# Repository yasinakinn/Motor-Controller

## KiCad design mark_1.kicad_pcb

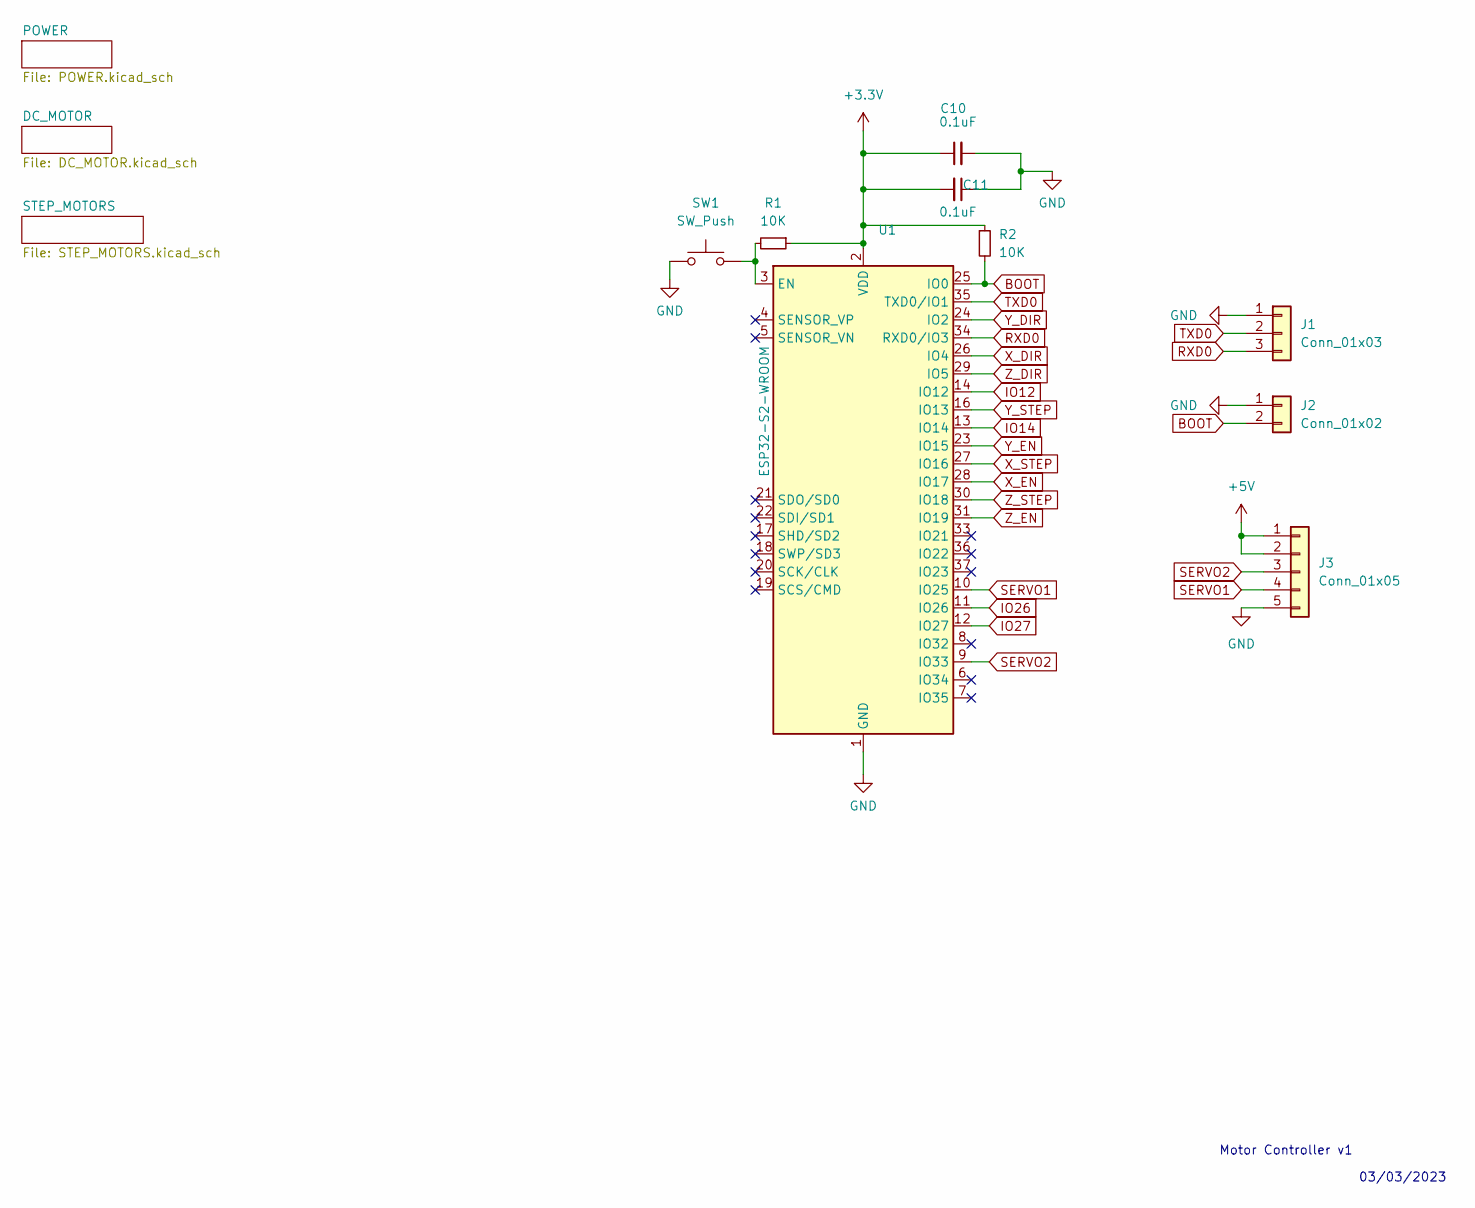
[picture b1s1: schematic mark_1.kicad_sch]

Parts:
C10, C11: 0.1uF; C_0805_2012Metric
J1: Conn_01x03; PinHeader_1x03_P2.54mm_Vertical
J2: Conn_01x02; PinHeader_1x02_P2.54mm_Vertical
J3: Conn_01x05; PhoenixContact_MC_1,5_5-G-3.81_1x05_P3.81mm_Horizontal
R1, R2: 10K; R_0805_2012Metric
SW1: SW_Push; SW_Push_1P1T_NO_6x6mm_H9.5mm
U1: ESP32-S2-WROOM; ESP32-WROOM-32

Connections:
+3.3V: C10.1, C11.2, R1.1, R2.1, U1.2 (VDD); also elsewhere on the board
+5V: J3.1, J3.2; also elsewhere on the board
BOOT: J2.2, R2.2, U1.25 (IO0)
GND: C10.2, C11.1, J1.1, J2.1, J3.5, SW1.1, U1.1 (GND), U1.15 (GND), U1.38 (GND), U1.39 (GND); also elsewhere on the board
IO12: U1.14 (IO12); also elsewhere on the board
IO14: U1.13 (IO14); also elsewhere on the board
IO26: U1.11 (IO26); also elsewhere on the board
IO27: U1.12 (IO27); also elsewhere on the board
unnamed: R1.2, SW1.2, U1.3 (EN)
RXD0: J1.3, U1.34 (RXD0/IO3)
SERVO1: J3.4, U1.10 (IO25)
SERVO2: J3.3, U1.9 (IO33)
TXD0: J1.2, U1.35 (TXD0/IO1)
X_DIR: U1.26 (IO4); also elsewhere on the board
X_EN: U1.28 (IO17); also elsewhere on the board
X_STEP: U1.27 (IO16); also elsewhere on the board
Y_DIR: U1.24 (IO2); also elsewhere on the board
Y_EN: U1.23 (IO15); also elsewhere on the board
Y_STEP: U1.16 (IO13); also elsewhere on the board
Z_DIR: U1.29 (IO5); also elsewhere on the board
Z_EN: U1.31 (IO19); also elsewhere on the board
Z_STEP: U1.30 (IO18); also elsewhere on the board

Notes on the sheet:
Motor Controller v1
03/03/2023

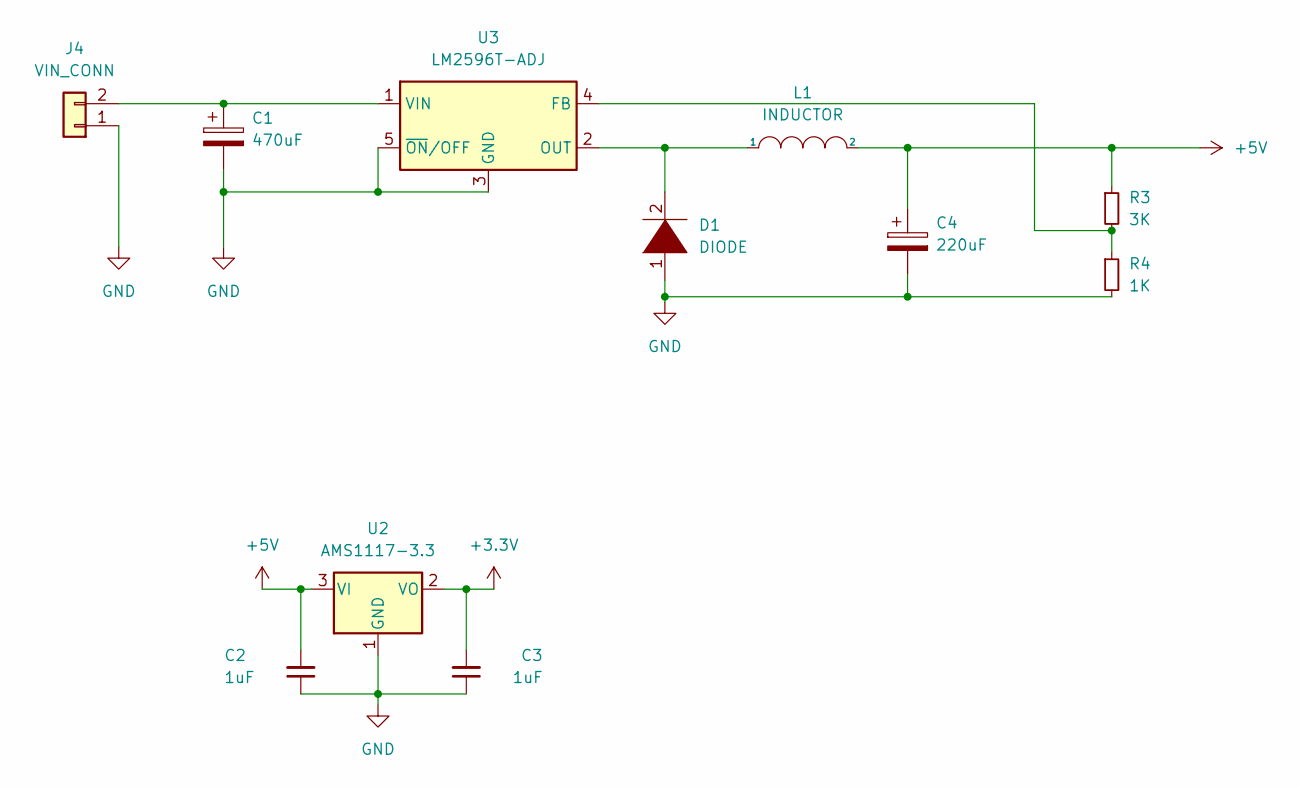
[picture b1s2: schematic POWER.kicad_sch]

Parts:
C1: 470uF; CP_Elec_8x6.7
C2, C3: 1uF; C_0805_2012Metric
C4: 220uF; CP_Elec_8x6.7
D1: DIODE; D_SMC
J4: VIN_CONN; PhoenixContact_MC_1,5_2-G-3.81_1x02_P3.81mm_Horizontal
L1: INDUCTOR; L_12x12mm_H6mm
R3: 3K; R_0805_2012Metric
R4: 1K; R_0805_2012Metric
U2: AMS1117-3.3; SOT-223-3_TabPin2
U3: LM2596T-ADJ; TO-263-5_TabPin3

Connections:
+3.3V: C3.2, U2.2 (VO); also elsewhere on the board
+5V: C2.2, C4.1, L1.2, R3.1, U2.3 (VI); also elsewhere on the board
GND: C1.2, C2.1, C3.1, C4.2, D1.1 (K), J4.1, R4.2, U2.1 (GND), U3.3 (GND), U3.5 (~ON/OFF); also elsewhere on the board
unnamed: C1.1, J4.2, U3.1 (VIN)
unnamed: D1.2 (A), L1.1, U3.2 (OUT)
unnamed: R3.2, R4.1, U3.4 (FB)

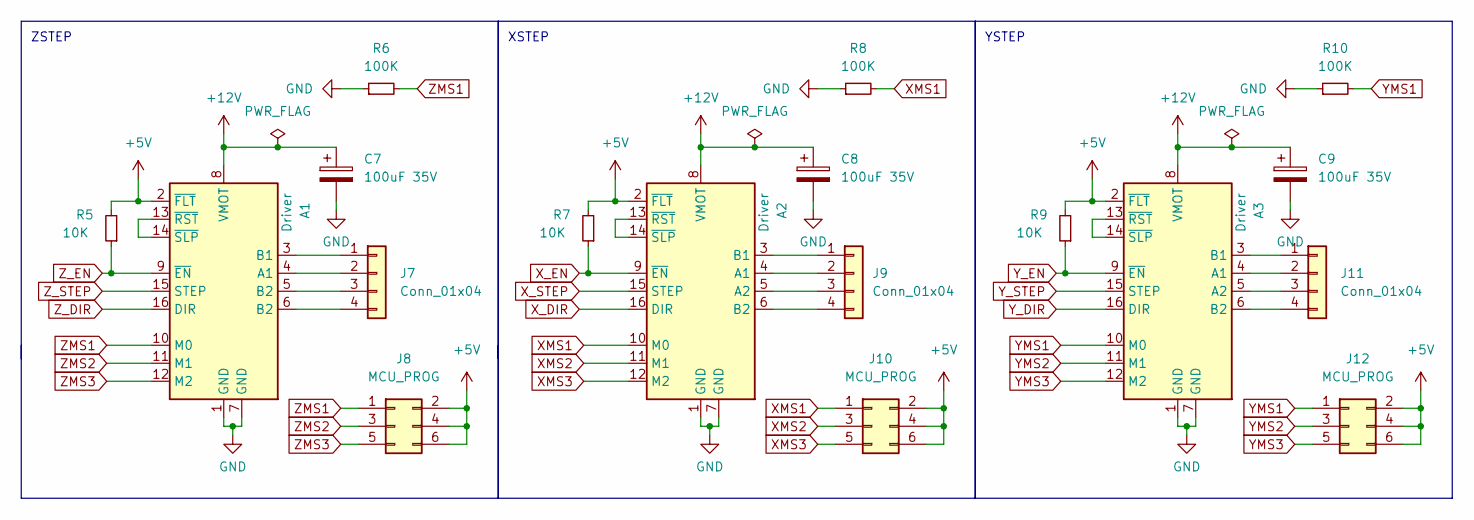
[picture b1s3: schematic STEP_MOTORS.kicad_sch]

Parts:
A1, A2, A3: Driver; Pololu_Breakout-16_15.2x20.3mm
C7, C8, C9: 100uF 35V; CP_Elec_6.3x7.7
J7, J9, J11: Conn_01x04; PhoenixContact_MC_1,5_4-G-3.81_1x04_P3.81mm_Horizontal
J8, J10, J12: MCU_PROG; PinHeader_2x03_P2.54mm_Vertical
R5, R7, R9: 10K; R_0805_2012Metric_Pad1.20x1.40mm_HandSolder
R6, R8, R10: 100K; R_0805_2012Metric_Pad1.20x1.40mm_HandSolder

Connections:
+5V: A1.2 (~FLT), A2.2 (~FLT), A3.2 (~FLT), J8.2, J8.4, J8.6, J10.2, J10.4, J10.6, J12.2, J12.4, J12.6, R5.2, R7.2, R9.2; also elsewhere on the board
+12V: A1.8 (VMOT), A2.8 (VMOT), A3.8 (VMOT), C7.1, C8.1, C9.1
GND: A1.1 (GND), A1.7 (GND), A2.1 (GND), A2.7 (GND), A3.1 (GND), A3.7 (GND), C7.2, C8.2, C9.2, R6.1, R8.1, R10.1; also elsewhere on the board
unnamed: A1.3 (B1), J7.1
unnamed: A1.4 (A1), J7.2
unnamed: A1.5 (B2), J7.3
unnamed: A1.6 (B2), J7.4
unnamed: A1.13 (~RST), A1.14 (~SLP)
unnamed: A2.3 (B1), J9.1
unnamed: A2.4 (A1), J9.2
unnamed: A2.5 (A2), J9.3
unnamed: A2.6 (B2), J9.4
unnamed: A2.13 (~RST), A2.14 (~SLP)
unnamed: A3.3 (B1), J11.1
unnamed: A3.4 (A1), J11.2
unnamed: A3.5 (A2), J11.3
unnamed: A3.6 (B2), J11.4
unnamed: A3.13 (~RST), A3.14 (~SLP)
XMS1: A2.10 (M0), J10.1, R8.2
XMS2: A2.11 (M1), J10.3
XMS3: A2.12 (M2), J10.5
X_DIR: A2.16 (DIR); also elsewhere on the board
X_EN: A2.9 (~EN), R7.1; also elsewhere on the board
X_STEP: A2.15 (STEP); also elsewhere on the board
YMS1: A3.10 (M0), J12.1, R10.2
YMS2: A3.11 (M1), J12.3
YMS3: A3.12 (M2), J12.5
Y_DIR: A3.16 (DIR); also elsewhere on the board
Y_EN: A3.9 (~EN), R9.1; also elsewhere on the board
Y_STEP: A3.15 (STEP); also elsewhere on the board
ZMS1: A1.10 (M0), J8.1, R6.2
ZMS2: A1.11 (M1), J8.3
ZMS3: A1.12 (M2), J8.5
Z_DIR: A1.16 (DIR); also elsewhere on the board
Z_EN: A1.9 (~EN), R5.1; also elsewhere on the board
Z_STEP: A1.15 (STEP); also elsewhere on the board

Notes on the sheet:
XSTEP
YSTEP
ZSTEP

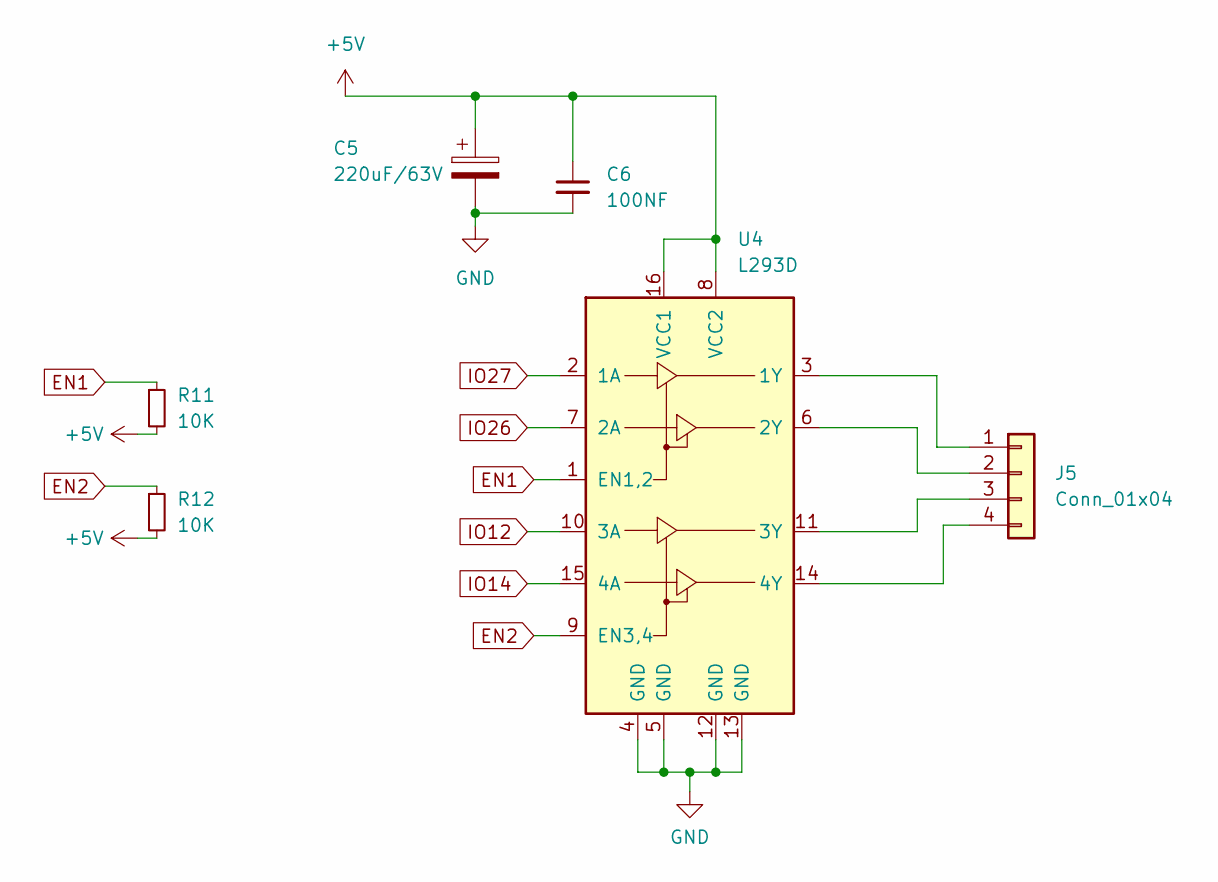
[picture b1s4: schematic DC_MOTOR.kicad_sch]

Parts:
C5: 220uF/63V; CP_Elec_8x6.7
C6: 100NF; C_0805_2012Metric
J5: Conn_01x04; PhoenixContact_MC_1,5_4-G-3.81_1x04_P3.81mm_Horizontal
R11, R12: 10K; R_0603_1608Metric
U4: L293D; DIP-16_W7.62mm

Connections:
+5V: C5.1, C6.1, R11.2, R12.2, U4.8 (VCC2), U4.16 (VCC1); also elsewhere on the board
EN1: R11.1, U4.1 (EN1,2)
EN2: R12.1, U4.9 (EN3,4)
GND: C5.2, C6.2, U4.4 (GND), U4.5 (GND), U4.12 (GND), U4.13 (GND); also elsewhere on the board
IO12: U4.10 (3A); also elsewhere on the board
IO14: U4.15 (4A); also elsewhere on the board
IO26: U4.7 (2A); also elsewhere on the board
IO27: U4.2 (1A); also elsewhere on the board
unnamed: J5.1, U4.3 (1Y)
unnamed: J5.2, U4.6 (2Y)
unnamed: J5.3, U4.11 (3Y)
unnamed: J5.4, U4.14 (4Y)

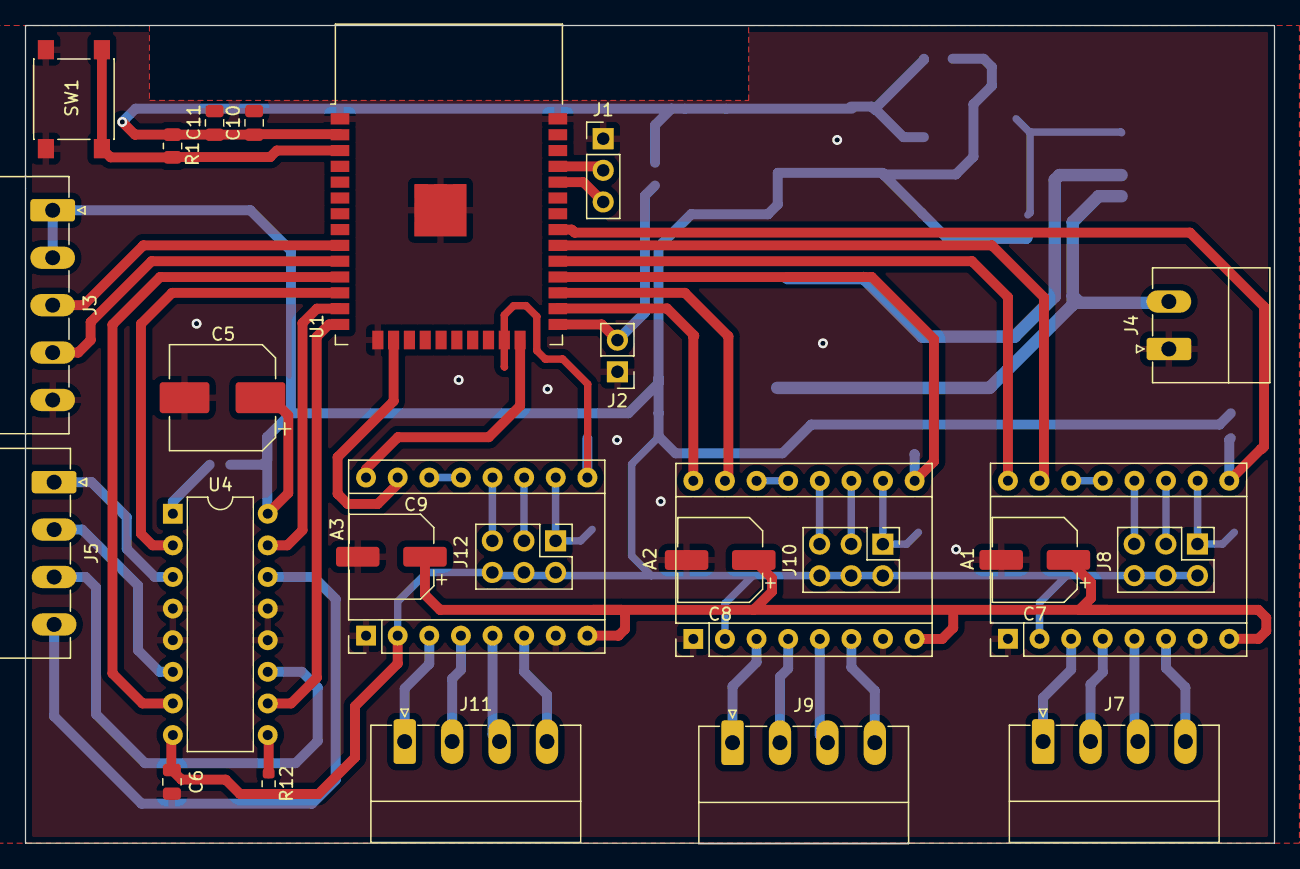
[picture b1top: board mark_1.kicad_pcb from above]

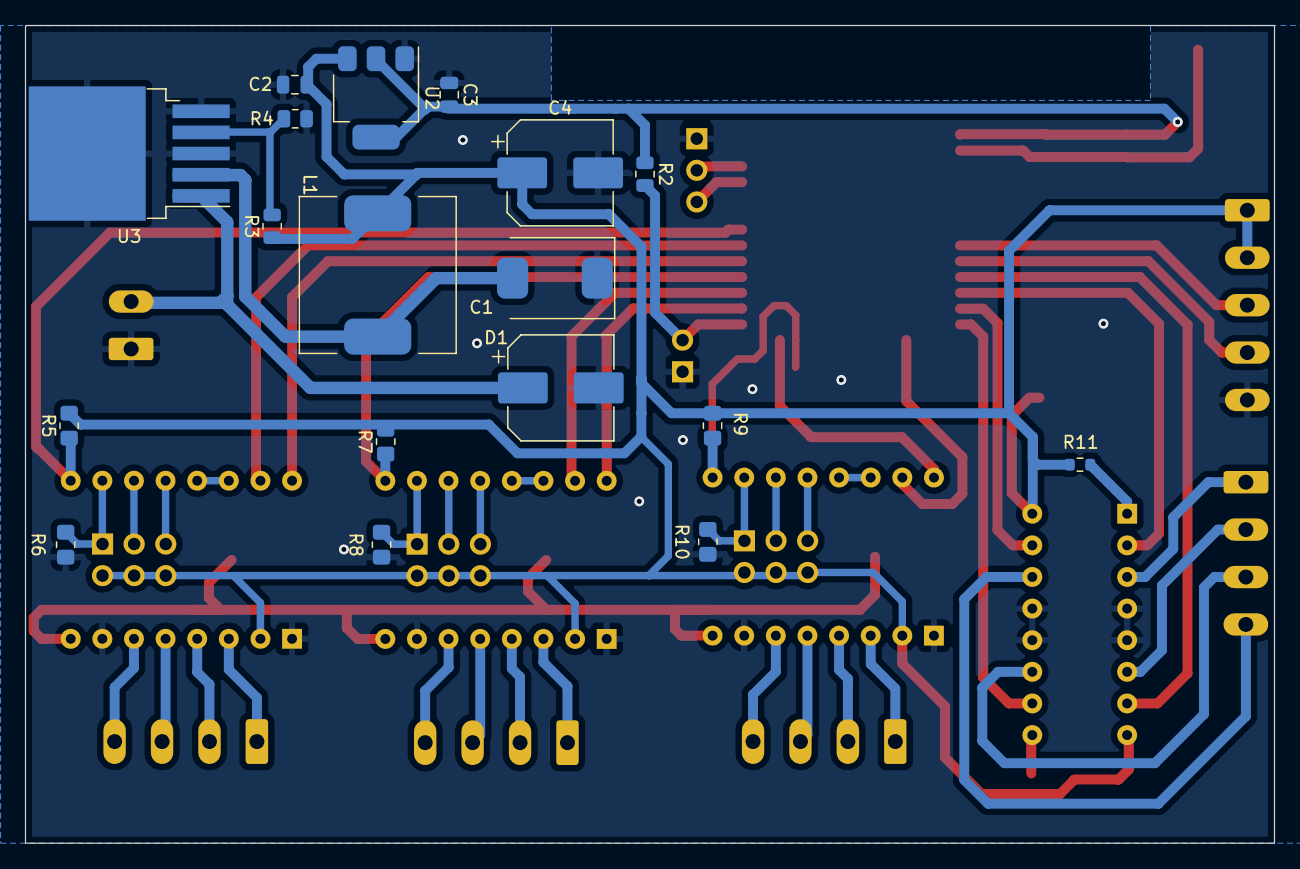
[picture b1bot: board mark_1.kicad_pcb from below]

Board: 2 copper layers, 100.3 x 65.7 mm, 44 parts (18 on the bottom side), 56 nets.

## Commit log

2023-03-08 ss added
2023-05-09 Backups and updates
